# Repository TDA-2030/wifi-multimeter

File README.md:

# WiFi Multimeter

A mini multimeter based on ESP32, that display the result on web page.

## Features

- Web page as monitor

- Portable, small size

- Voice announcements

## Functions

  - voltage: ±400V, ±60V, ±2V

  - current: ±10A, ±2A, ±10mA

  - resistance: 1KΩ, 200KΩ, 10MΩ

  - buzzer

  - power
  
  - diode drop voltage

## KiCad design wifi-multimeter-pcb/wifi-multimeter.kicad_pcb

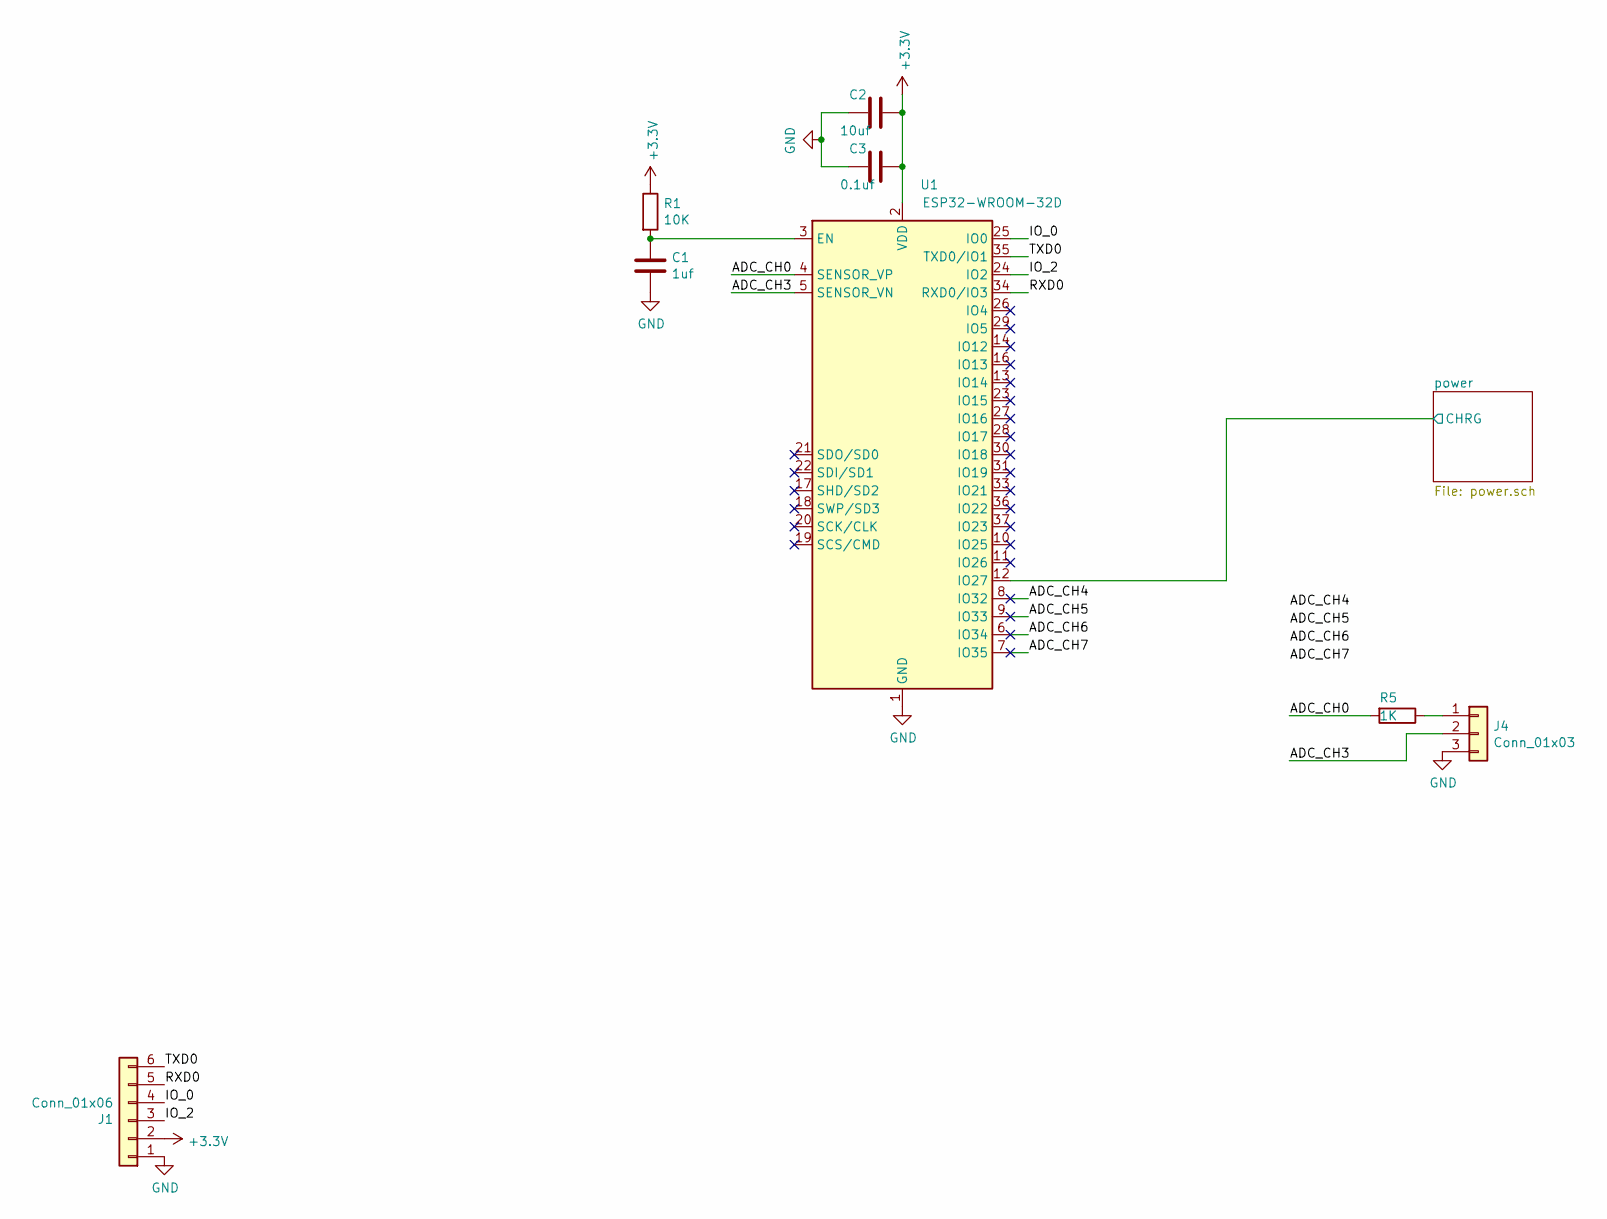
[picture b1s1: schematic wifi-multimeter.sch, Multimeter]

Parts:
C1: 1uf; C_0603_1608Metric
C2: 10uf; C_0805_2012Metric
C3: 0.1uf; C_0402_1005Metric
J1: Conn_01x06; PinHeader_1x06_P2.54mm_Vertical
J4: Conn_01x03; PinHeader_1x03_P2.54mm_Horizontal
R1: 10K; R_0402_1005Metric
R5: 1K; R_0402_1005Metric
U1: ESP32-WROOM-32D; ESP32-WROOM-32

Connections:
+3V3: C2.1, C3.1, J1.2, R1.1, U1.2 (VDD); also elsewhere on the board
/ADC_CH0: R5.2, U1.4 (SENSOR_VP)
/ADC_CH3: J4.2, U1.5 (SENSOR_VN)
/ADC_CH4: U1.8 (IO32)
/ADC_CH5: U1.9 (IO33)
/ADC_CH6: U1.6 (IO34)
/ADC_CH7: U1.7 (IO35)
/IO_0: J1.4, U1.25 (IO0)
/IO_2: J1.3, U1.24 (IO2)
/RXD0: J1.5, U1.34 (RXD0/IO3)
/TXD0: J1.6, U1.35 (TXD0/IO1)
/power/CHRG: U1.12 (IO27); also elsewhere on the board
GND: C1.2, C2.2, C3.2, J1.1, J4.3, U1.1 (GND), U1.15 (GND), U1.38 (GND), U1.39 (GND); also elsewhere on the board
unnamed: C1.1, R1.2, U1.3 (EN)
unnamed: J4.1, R5.1

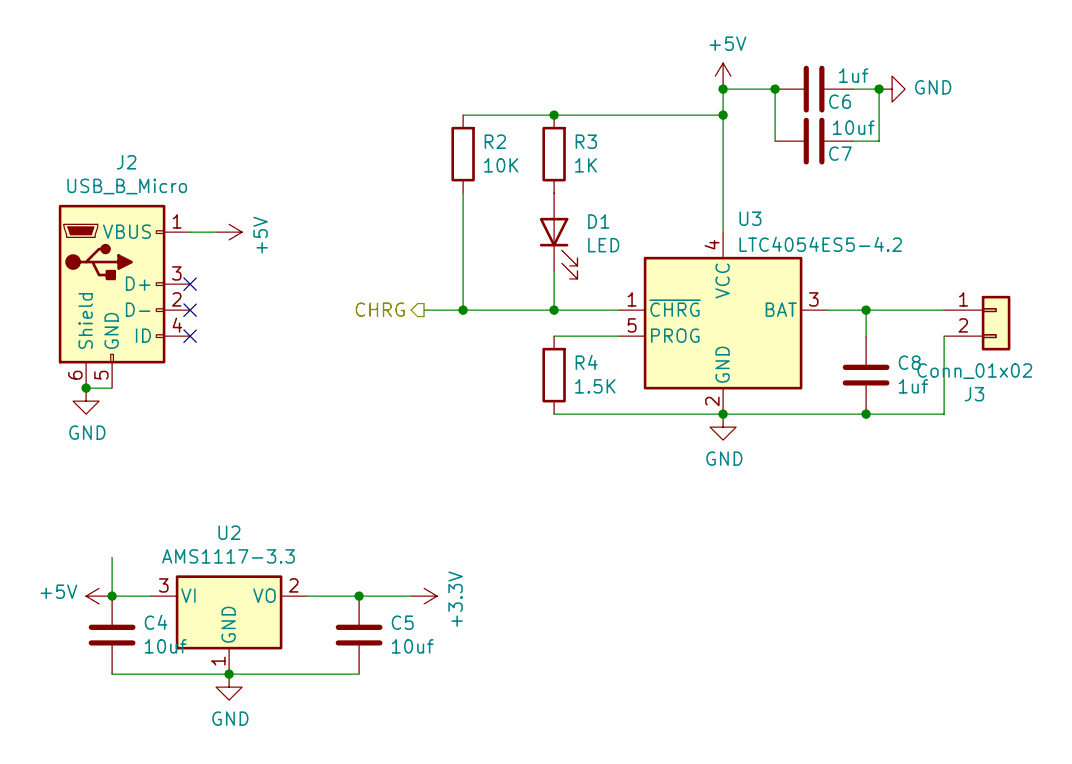
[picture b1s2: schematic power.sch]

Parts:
C4, C5, C7: 10uf; C_0805_2012Metric
C6, C8: 1uf; C_0603_1608Metric
D1: LED; LED_0603_1608Metric
J2: USB_B_Micro; USB_Micro-B_Wuerth_629105150521
J3: Conn_01x02; PinHeader_1x02_P2.54mm_Vertical
R2: 10K; R_0402_1005Metric
R3: 1K; R_0402_1005Metric
R4: 1.5K; R_0402_1005Metric
U2: AMS1117-3.3; SOT-223-3_TabPin2
U3: LTC4054ES5-4.2; TSOT-23-5

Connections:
+3V3: C5.1, U2.2 (VO); also elsewhere on the board
+5V: C4.1, C6.2, C7.2, J2.1 (VBUS), R2.2, R3.2, U2.3 (VI), U3.4 (VCC)
/power/CHRG: D1.1 (K), R2.1, U3.1 (~CHRG); also elsewhere on the board
GND: C4.2, C5.2, C6.1, C7.1, C8.2, J2.5 (GND), J2.6 (Shield), J3.2, R4.1, U2.1 (GND), U3.2 (GND); also elsewhere on the board
unnamed: C8.1, J3.1, U3.3 (BAT)
unnamed: D1.2 (A), R3.1
unnamed: R4.2, U3.5 (PROG)

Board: 2 copper layers, 21 parts (0 on the bottom side), 15 nets, no tracks yet.

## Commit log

2020-07-24 feat: add wed page
2020-07-24 fix: update favicon
2020-07-25 feat: add web page 4 button
2020-07-26 feat: add speech files
2020-07-27 fix: add gitignore for folder speech
2020-07-27 feat: add speech
2020-07-27 feat: add speech list
2020-07-29 feat: first complete speech
2020-07-29 feat: add file manage
2020-07-30 feat: add settings page
2020-07-30 fix: remove the redundant audio files
2020-07-30 feat: add PCB files
2020-08-02 feat: add ADS1115 and INA226 code
2020-08-02 feat: add reference files
2020-08-03 fix: ADS1115
2020-08-16 update pcb
2020-08-19 fix: i2c_bus and ina226
2020-08-21 fix: update speech play string
2020-08-22 feat: add check audio file is updated
2020-08-22 fix: speech string issue
2020-08-22 style: rename components web to web-dashboard
2021-02-04 fix: replace blufi with webconfig
2021-02-04 add simulation folder
2021-02-06 draft
